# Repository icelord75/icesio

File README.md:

# iCESIO

**A replacement brain for the CASIO 3208 module** — the one inside the CA-53W and CA-506 calculator watches.
iCESIO keeps the original case, LCD, keypad and buzzer, and swaps the stock chip for a PIC16 microcontroller
with an accelerometer, a compass, an environmental sensor and a full RGB backlight.

<p align="center">
  
  &nbsp;&nbsp;
  
</p>

> **Status:** work in progress. The hardware (rev. V2) is done; the firmware shows and sets the time,
> beeps and talks to the sensors over I²C. Most of the watch features listed below are still to come.

---

## Contents

- [Hardware](#hardware)
- [Firmware](#firmware)
  - [What works](#what-works)
  - [Using the watch](#using-the-watch)
  - [Building](#building)
  - [Configuration](#configuration)
- [Repository layout](#repository-layout)
- [Known issues](#known-issues)
- [Roadmap](#roadmap)
- [Related projects](#related-projects)
- [License](#license)

---

## Hardware

| Function       | Part                                                              | Notes                                         |
|----------------|-------------------------------------------------------------------|-----------------------------------------------|
| MCU            | Microchip **PIC16F19197**                                         | 8-bit, 56 KB flash, 4 KB RAM, 256 B EEPROM, LCD driver, RTCC |
| EEPROM         | Microchip **24CW1280T-I/CS0668**                                  | 16 KB, WLCSP                                  |
| Accelerometer  | NXP **MMA8451QT**                                                 | 3-axis, 14-bit / 8-bit                        |
| Compass        | Honeywell **HMC5883L** or Isentek **IST8310**                     | 3-axis magnetometer                           |
| Environment    | Bosch **BME280**                                                  | temperature, humidity, pressure               |
| RGB backlight  | ON Semi **NCP5623CMUTBG** + Songxin **SX-0402-RGB**               | I²C triple LED driver, 0404 RGB LED           |
| Battery        | **CR2016**                                                        | CR2020 / CR2025 / CR2320 might fit            |

All peripherals share one I²C bus. A 19200 bps TTL UART is available for debugging.

<p align="center">
  
</p>

### Connections to the CASIO module

| CASIO pad      | MCU pin          | Use                                                      |
|----------------|------------------|----------------------------------------------------------|
| MODE           | RH0              | side button, active low (connects to GND, weak pull-up)  |
| PRGM           | RH1              | side button, active low (connects to GND, weak pull-up)  |
| SIG            | RG0 (PWM3 via PPS) | buzzer, through T1 (PDTC114) and the coil L1           |
| K2…K5          | RG1, RG2, RG3, RF7 | keypad rows (driven low)                               |
| K6…K9          | RC7, RC6, RC0, RC1 | keypad columns (inputs, weak pull-ups)                 |
| LCD_S0…S30, C0…C3 | LCD SEG/COM pins | 4-COM multiplexed LCD                                |

---

## Firmware

MPLAB X project in [`icesio.X/`](icesio.X), written in C for **MPLAB XC8**. Peripheral setup is generated
by MPLAB Code Configurator (`icesio.mc3`, [`mcc_generated_files/`](icesio.X/mcc_generated_files)).

| Module                                   | What it does                                                        |
|------------------------------------------|---------------------------------------------------------------------|
| [`main.c`](icesio.X/main.c)              | power-on self test over UART, main loop (100 ms tick)               |
| [`clock.c`](icesio.X/clock.c)            | time screen and time / date setting                                 |
| [`buttons.c`](icesio.X/buttons.c)        | MODE / PRGM debouncing, auto-repeat                                 |
| [`beep.c`](icesio.X/beep.c)              | buzzer: ~4 kHz hardware PWM, key click                              |
| [`keypad.c`](icesio.X/keypad.c)          | 4×4 keypad matrix scan with debouncing                              |
| [`lcd.c`](icesio.X/lcd.c)                | 7-segment font and table-driven LCD segment mapping                 |
| [`led.c`](icesio.X/led.c)                | NCP5623C RGB LED driver                                             |
| [`bme280.c`](icesio.X/bme280.c)          | BME280 temperature / humidity / pressure                            |
| [`mma8451.c`](icesio.X/mma8451.c)        | MMA8451 accelerometer (based on [yangosoft/pic_mma8451](https://github.com/yangosoft/pic_mma8451)) |
| [`compass.c`](icesio.X/compass.c)        | HMC5883L compass (disabled for now)                                 |
| [`uart.c`](icesio.X/uart.c), [`debug.h`](icesio.X/debug.h) | debug output: `DBG_PRINT()` / `DBG_PRINTF()`, compiled only with `DEBUG` |

### What works

- [x] Power-on self test with progress on the debug UART (`DEBUG` builds)
- [x] Time display with a blinking colon and the day of month
- [x] Setting time and date with the side buttons or the keypad
- [x] Rate correction in s/day, stored in EEPROM
- [x] Key click on the buzzer
- [x] 4×4 keypad driver (test mode shows the pressed key)
- [x] RGB LED, BME280, MMA8451 and HMC5883L drivers
- [ ] Alarms, stopwatch, timer, calculator… — see the [roadmap](#roadmap)

### Using the watch

```
digit:  0 1 2 3 4 5 6 7     9 10
time:   H H : M M   S S     D  D      D D = day of month
date:   D D - M M - Y Y               shown while setting the date
```

| Mode        | Button   | Action                                                                 |
|-------------|----------|------------------------------------------------------------------------|
| Time        | **PRGM** | enter setting mode                                                     |
| Setting     | **PRGM** | next field: hour → minute → second → year → month → day → rate correction → done |
| Setting     | **MODE** | +1 to the blinking field; hold to scroll                               |
| Seconds     | **MODE** | reset to `00` and start the clock right away — press it on the time signal |
| Setting     | **0…9**  | type the field: two digits set it and jump to the next field (`1_` after the first digit) |
| Setting     | **=**    | same as PRGM; a single typed digit counts as `0x`                      |
| Setting     | **+ / −** | +1 / −1 to the field (on seconds: reset to `00`)                      |
| Setting     | **.**    | finish setting                                                         |
| Correction  | **MODE / +**, **−** | rate correction ±1 s/day; hold to repeat, after 3 s in steps of 10 |

Keypad (from the goodwatch firmware for the same module, matches the CA-53W):

|        | K6 | K7 | K8 | K9 |
|--------|:--:|:--:|:--:|:--:|
| **K5** | 7  | 8  | 9  | ÷  |
| **K4** | 4  | 5  | 6  | ×  |
| **K3** | 1  | 2  | 3  | −  |
| **K2** | 0  | .  | =  | +  |

With `KEYPAD_TEST` on, a key pressed on the time screen is shown as `KEY    7` for one second.

Typed values are checked: hours 00–23, minutes and seconds 00–59, year 00–99, month 01–12, and the day
must exist in that month (no 31 April, 29 February only in leap years). An impossible value is rejected
with a long beep. Typing the seconds starts the clock at the entered time immediately.

### Rate correction

Without a 32.768 kHz crystal the clock runs from the internal MFINTOSC, which can be off by up to ~2 %
(about ±1700 s/day). The last setting field, `Cor  -12`, holds a correction in **seconds per day**
(−1999…+1999), saved in the data EEPROM:

1. Set the time exactly and note how many seconds the watch gains or loses over a day or more.
2. Enter the measured drift per day with the opposite sign: the watch **gains** 12 s/day → `Cor -12`;
   it **loses** 300 s/day → `Cor 300`.

The firmware then moves the RTCC seconds by one every 86400 / |Cor| seconds, so the watch stays within
about a second. (The hardware `RTCCAL` register only reaches about ±6 s/day, too little for MFINTOSC.)

Setting mode also ends after 60 s without a press; changes are kept. Only the fields you changed are
written back, so entering and leaving setting mode never makes the clock lose time. The day of the week
is calculated automatically.

### Building

Requirements:

- [MPLAB X IDE](https://www.microchip.com/mplab/mplab-x-ide) (tested with v6.35)
- [MPLAB XC8](https://www.microchip.com/mplab/compilers) **v3.10**
- Device pack **PIC16F1xxxx_DFP 1.7.146**

Open `icesio.X` in MPLAB X and build, or from the command line (after MPLAB X has generated
`nbproject/Makefile-local-default.mk` for your machine):

```bash
cd icesio.X
make -f nbproject/Makefile-default.mk CONF=default .build-conf
```

Current size: **~6.0 K of 32 K words** program memory (18 %), **324 B** RAM; with `DEBUG` ~11.7 K (printf).

### Configuration

Compile-time switches, all at the top of their source files:

| Define              | File        | Default | Meaning                                                    |
|---------------------|-------------|---------|------------------------------------------------------------|
| `CLOCK_24H`         | `clock.c`   | `1`     | 24-hour display; `0` for 12-hour with AM/PM                 |
| `KEY_BEEP`          | `clock.c`   | `1`     | click on every button / key press                          |
| `KEYPAD_TEST`       | `clock.c`   | `1`     | show the pressed key on the time screen                    |
| `KEYPAD_ROW_K2`     | `keypad.c`  | `1`     | scan the bottom row on RG1; `0` keeps RG1 as UART TX       |
| `SET_TIMEOUT_S`     | `clock.c`   | `60`    | leave setting mode after this many seconds                 |
| `BTN_ACTIVE_LOW`    | `buttons.c` | `1`     | buttons connect to GND (`1`, as on goodwatch) or to + (`0`) |
| `BTN_SOFT_PULLDOWN` | `buttons.c` | `1`     | with `BTN_ACTIVE_LOW 0` only: software pull-down (no resistors to GND) |
| `BEEP_PR`           | `beep.c`    | `14`    | tone: 62.5 kHz / (`BEEP_PR` + 1) ≈ 4167 Hz                 |
| `BEEP_CLICK_MS`     | `beep.c`    | `30`    | key click length                                           |
| `USE_COMPASS`       | `main.c`    | `0`     | initialise and poll the compass                            |
| `DEBUG`             | `debug.h`   | off     | self-test log and a sensor dump every second on the UART (19200 bps, RG1) |
| `COR_MAX`           | `clock.c`   | `1999`  | rate correction limit, s/day                               |

---

## Repository layout

```
icesio.X/              firmware (MPLAB X project)
hardware/
  icesio.sch/.brd      Eagle, rev. V1
  icesio_V2.sch/.brd   Eagle, rev. V2
  icesio_V2/           rev. V2 imported into KiCad
  CHAGE LIST           V1 → V2 changes
kicad/                 KiCad import of icesio0
icesio0.*, icesio2.*   Eagle snapshots (2019)
icesio2_2019-03-12.zip Gerber + drill files of the 2019-03-12 board
icesio.docx            draft of the operation guide
front.png, back.png    board renders
schematic.png          schematic, rev. V2
```

---

## Known issues

- **RTCC runs from MFINTOSC.** The SOSC crystal pins are used by the keypad, so the clock runs from the
  internal oscillator (about ±1–2 %, and it drifts with temperature). The [rate correction](#rate-correction)
  compensates the average error; a 32.768 kHz crystal is planned for the next board revision.
- **SEG17 / SEG20 share the ICSP CLK / DAT pins.** Eight segments are lost while debugging
  (`#ifndef __DEBUG` in `lcd.c`). To be rerouted in the next revision.
- **Debug UART vs. keypad.** K2 (RG1) is also the EUSART2 TX pin. The UART exists only in `DEBUG` builds;
  normal builds switch EUSART2 off and give RG1 to the keypad, debug builds keep the UART there and don't
  scan the bottom row (0 . = +).
- **SOSC and LCD pins used by the keypad.** `Keypad_Init()` switches off the secondary oscillator
  (RC0/RC1) and the unused LCD segments SEG27/SEG28 (RC6/RC7) that MCC had enabled.
- The keypad layout comes from goodwatch and has not been checked on this board yet.

---

## Roadmap

- **Controls:** 2 side buttons + 4×4 keypad
- **Timekeeping:** home and world time with automatic DST and assisted calibration
- **Perpetual calendar** up to 2199
- **Calculator:** infix, prefix or RPN (configurable), ±9.9999999 × 10<sup>99</sup> (8-digit mantissa)
- **Alarm:** 5 daily + 5 weekly alarms, hourly signal
- **Stopwatch:** 5 stopwatches up to 23:59:59.99, 0.01 s resolution
- **Timer:** 5 countdown timers up to 99:59:59
- **Signals:** RTTTL melodies for alarms and timers; minute repeater
- **Backlight:** full RGB, separate colours for alarms and timers
- **Sun and Moon:** sunrise / sunset (latitude presets + time zone), precise Moon phase, equation of time
- **Accelerometer:** tap control, tilt sensor, speedometer, 0–100 km/h timing
- **Compass:** regular compass, angle finder
- **Environment:** temperature (°C / °F), humidity, barometer (hPa, mbar, at, atm, Torr, mmHg, PSI, inHg),
  with hour / 12 h / 24 h trends

---

## Related projects

- [**goodwatch**](https://github.com/travisgoodspeed/goodwatch) — replacement board for the same CASIO 3208
  module (CA-53W, CA-506), based on the CC430
- [**Pluto**](https://github.com/carrotIndustries/pluto) — replacement PCB for the CASIO F-91W, based on an MSP430

---

## License

[MIT](LICENSE) © icelord75 — firmware, hardware design files and documentation.

Exceptions: files in [`icesio.X/mcc_generated_files/`](icesio.X/mcc_generated_files) are generated by
MPLAB Code Configurator and covered by Microchip's license terms in their headers;
[`mma8451.c`](icesio.X/mma8451.c) is based on [yangosoft/pic_mma8451](https://github.com/yangosoft/pic_mma8451).

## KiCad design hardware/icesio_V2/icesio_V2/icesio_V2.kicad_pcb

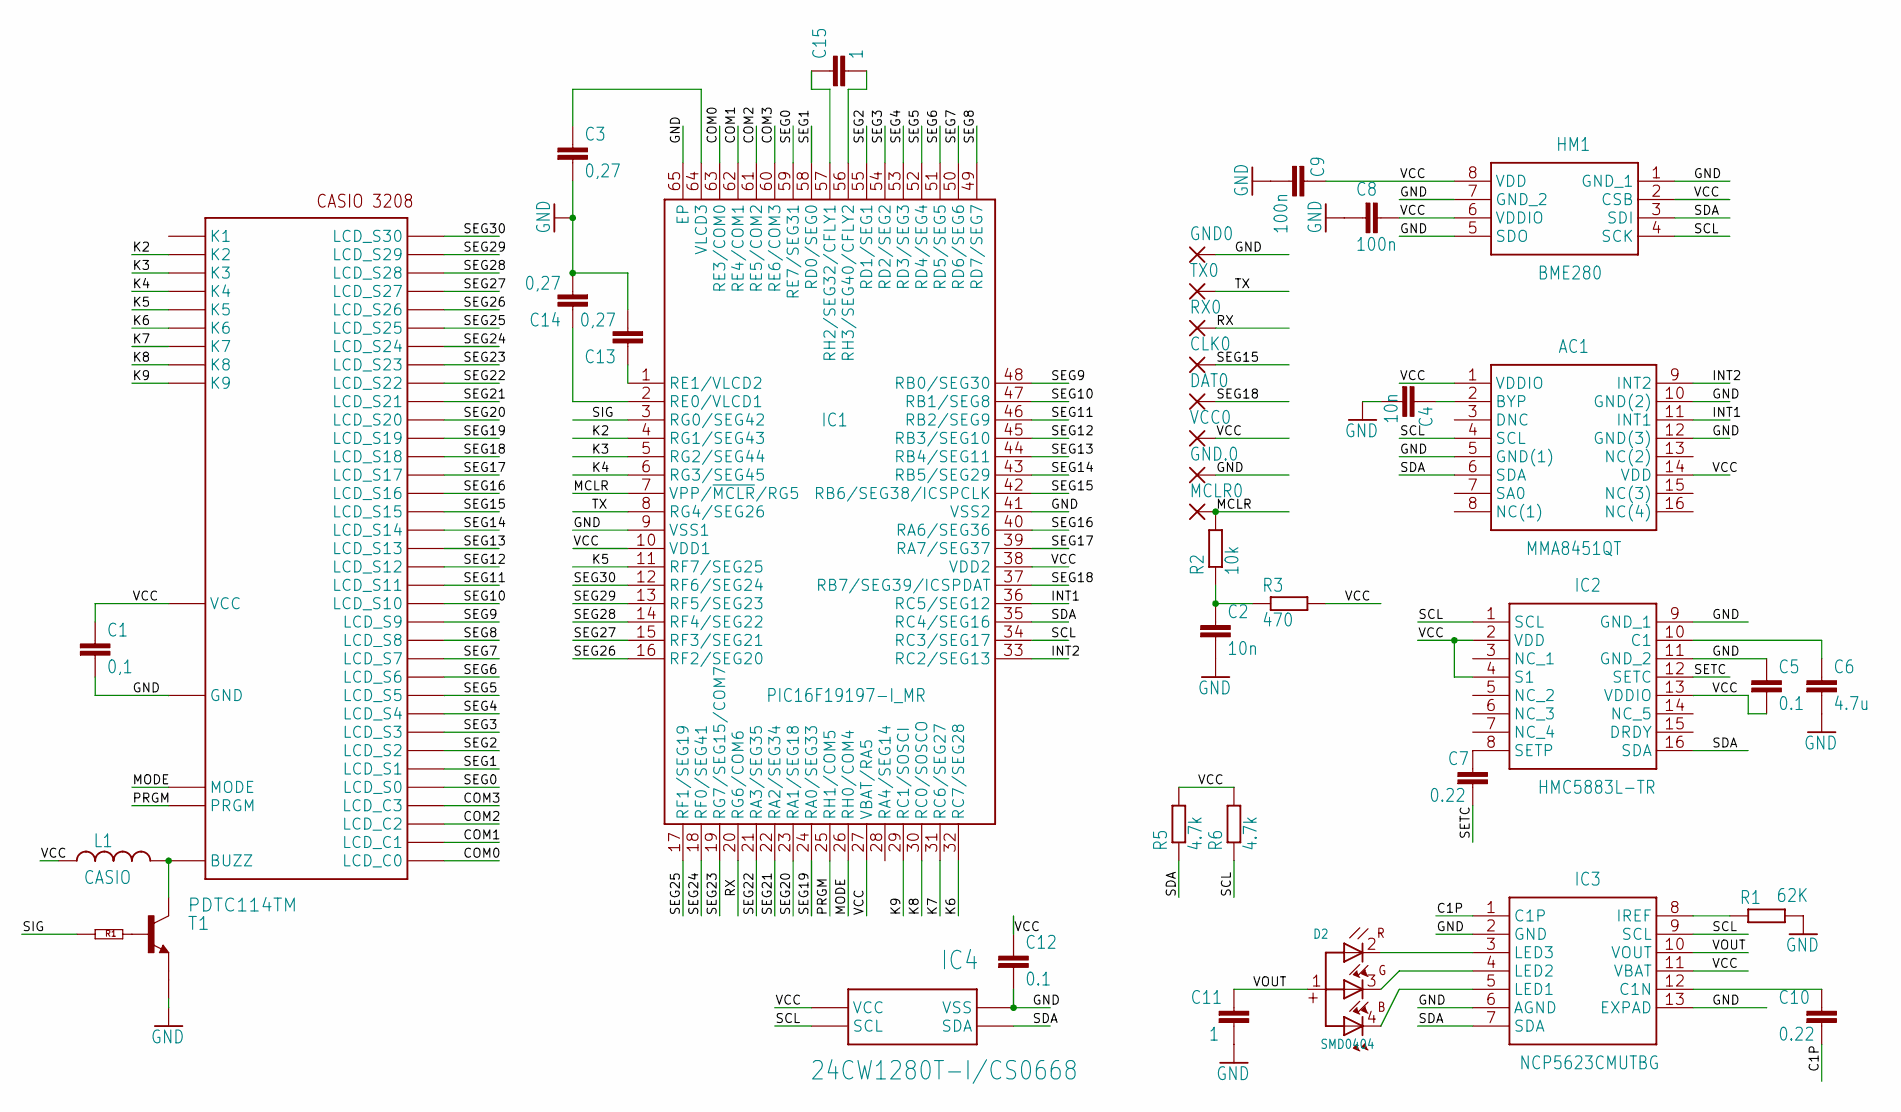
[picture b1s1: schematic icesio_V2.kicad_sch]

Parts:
AC1: MMA8451QT; PQFN50P300X300X100-16N
C1: 0,1; RESC0402_L
C2, C4: 10n; RESC0402_L
C3, C13, C14: 0,27; RESC0402_L
C5, C12: 0.1; RESC0402_L
C6: 4.7u; RESC0402_L
C7, C10: 0.22; RESC0402_L
C8, C9: 100n; RESC0402_L
C11, C15: 1; RESC0402_L
CLK0: WIREPADSMD1,27-254; SMD1,27-2,54
D2: SMD0404; WL-SFCC_0404
DAT0: WIREPADSMD1,27-254; SMD1,27-2,54
GND0, GND.0: WIREPADSMD1,27-254; SMD1,27-2,54
HM1: BME280
IC1: PIC16F19197-I_MR; QFN50P900X900X100-65N
IC2: HMC5883L-TR; 16-PIN-LPCC
IC3: NCP5623CMUTBG; NCP5623BMUTBG
IC4: 24CW1280T-I/CS0668; CSP
L1: CASIO; L4516C
MCLR0: WIREPADSMD1,27-254; SMD1,27-2,54
R1: 62K; R0402
R2: 10k; R0402
R3: 470; R0402
R5, R6: 4.7k; R0402
RX0: WIREPADSMD1,27-254; SMD1,27-2,54
T1: PDTC114TM; SOT883(B)
TX0: WIREPADSMD1,27-254; SMD1,27-2,54
U$1: CASIO3208
VCC0: WIREPADSMD1,27-254; SMD1,27-2,54

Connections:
BUZ: L1.2, T1.3 (C), U$1.BUZZ
BYP: AC1.2 (BYP), C4.1
C1: C6.1, IC2.10 (C1)
C1P: C10.2, IC3.1 (C1P)
CFLY1: C15.1, IC1.57 (RH2/SEG32/CFLY1)
CFLY2: C15.2, IC1.56 (RH3/SEG40/CFLY2)
COM0: IC1.63 (RE3/COM0), U$1.LCD1 (LCD_C0)
COM1: IC1.62 (RE4/COM1), U$1.LCD2 (LCD_C1)
COM2: IC1.61 (RE5/COM2), U$1.LCD3 (LCD_C2)
COM3: IC1.60 (RE6/COM3), U$1.LCD4 (LCD_C3)
GND: AC1.5 (GND(1)), AC1.10 (GND(2)), AC1.12 (GND(3)), C1.2, C2.2, C3.2, C4.2, C5.1, C6.2, C8.2, C9.2, C11.2, C12.2, C13.2, C14.2, GND0.1, GND.0.1, HM1.1 (GND_1), HM1.5 (SDO), HM1.7 (GND_2), IC1.9 (VSS1), IC1.41 (VSS2), IC1.65 (EP), IC2.9 (GND_1), IC2.11 (GND_2), IC3.2 (GND), IC3.6 (AGND), IC3.13 (EXPAD), IC4.VSS, R1.2, T1.2 (E), U$1.GND
INT1: AC1.11 (INT1), IC1.36 (RC5/SEG12)
INT2: AC1.9 (INT2), IC1.33 (RC2/SEG13)
K2: IC1.4 (RG1/SEG43), U$1.K2
K3: IC1.5 (RG2/SEG44), U$1.K3
K4: IC1.6 (RG3/SEG45), U$1.K4
K5: IC1.11 (RF7/SEG25), U$1.K5
K6: IC1.32 (RC7/SEG28), U$1.K6
K7: IC1.31 (RC6/SEG27), U$1.K7
K8: IC1.30 (RC0/SOSCO), U$1.K8
K9: IC1.29 (RC1/SOSCI), U$1.K9
MCLR: IC1.7 (VPP/~MCLR/RG5), MCLR0.1, R2.2
MCLRVCC: C2.1, R2.1, R3.1
MODE: IC1.26 (RH0/COM4), U$1.MODE
unnamed: D2.2 (R), IC3.3 (LED3)
unnamed: C7.1, IC2.8 (SETP)
unnamed: D2.3 (G), IC3.4 (LED2)
unnamed: D2.4 (B), IC3.5 (LED1)
unnamed: IC3.8 (IREF), R1.1
unnamed: C10.1, IC3.12 (C1N)
PRGM: IC1.25 (RH1/COM5), U$1.PRGM
RX: IC1.20 (RG6/COM6), RX0.1
SCL: AC1.4 (SCL), HM1.4 (SCK), IC1.34 (RC3/SEG17), IC2.1 (SCL), IC3.9 (SCL), IC4.SCL, R6.1
SDA: AC1.6 (SDA), HM1.3 (SDI), IC1.35 (RC4/SEG16), IC2.16 (SDA), IC3.7 (SDA), IC4.SDA, R5.1
SEG0: IC1.59 (RE7/SEG31), U$1.LCD5 (LCD_S0)
SEG1: IC1.58 (RD0/SEG0), U$1.LCD6 (LCD_S1)
SEG2: IC1.55 (RD1/SEG1), U$1.LCD7 (LCD_S2)
SEG3: IC1.54 (RD2/SEG2), U$1.LCD8 (LCD_S3)
SEG4: IC1.53 (RD3/SEG3), U$1.LCD9 (LCD_S4)
SEG5: IC1.52 (RD4/SEG4), U$1.LCD10 (LCD_S5)
SEG6: IC1.51 (RD5/SEG5), U$1.LCD11 (LCD_S6)
SEG7: IC1.50 (RD6/SEG6), U$1.LCD12 (LCD_S7)
SEG8: IC1.49 (RD7/SEG7), U$1.LCD13 (LCD_S8)
SEG9: IC1.48 (RB0/SEG30), U$1.LCD14 (LCD_S9)
SEG10: IC1.47 (RB1/SEG8), U$1.LCD15 (LCD_S10)
SEG11: IC1.46 (RB2/SEG9), U$1.LCD16 (LCD_S11)
SEG12: IC1.45 (RB3/SEG10), U$1.LCD17 (LCD_S12)
SEG13: IC1.44 (RB4/SEG11), U$1.LCD18 (LCD_S13)
SEG14: IC1.43 (RB5/SEG29), U$1.LCD19 (LCD_S14)
SEG15: CLK0.1, IC1.42 (RB6/SEG38/ICSPCLK), U$1.LCD20 (LCD_S15)
SEG16: IC1.40 (RA6/SEG36), U$1.LCD21 (LCD_S16)
SEG17: IC1.39 (RA7/SEG37), U$1.LCD22 (LCD_S17)
SEG18: DAT0.1, IC1.37 (RB7/SEG39/ICSPDAT), U$1.LCD23 (LCD_S18)
SEG19: IC1.24 (RA0/SEG33), U$1.LCD24 (LCD_S19)
SEG20: IC1.23 (RA1/SEG18), U$1.LCD25 (LCD_S20)
SEG21: IC1.22 (RA2/SEG34), U$1.LCD26 (LCD_S21)
SEG22: IC1.21 (RA3/SEG35), U$1.LCD27 (LCD_S22)
SEG23: IC1.19 (RG7/SEG15/COM7), U$1.LCD28 (LCD_S23)
SEG24: IC1.18 (RF0/SEG41), U$1.LCD29 (LCD_S24)
SEG25: IC1.17 (RF1/SEG19), U$1.LCD30 (LCD_S25)
SEG26: IC1.16 (RF2/SEG20), U$1.LCD31 (LCD_S26)
SEG27: IC1.15 (RF3/SEG21), U$1.LCD32 (LCD_S27)
SEG28: IC1.14 (RF4/SEG22), U$1.LCD33 (LCD_S28)
SEG29: IC1.13 (RF5/SEG23), U$1.LCD34 (LCD_S29)
SEG30: IC1.12 (RF6/SEG24), U$1.LCD35 (LCD_S30)
SETC: C7.2, IC2.12 (SETC)
SIG: IC1.3 (RG0/SEG42), T1.1 (INPUT)
TX: IC1.8 (RG4/SEG26), TX0.1
VCC: AC1.1 (VDDIO), AC1.14 (VDD), C1.1, C5.2, C8.1, C9.1, C12.1, HM1.2 (CSB), HM1.6 (VDDIO), HM1.8 (VDD), IC1.10 (VDD1), IC1.27 (VBAT/RA5), IC1.38 (VDD2), IC2.2 (VDD), IC2.4 (S1), IC2.13 (VDDIO), IC3.11 (VBAT), IC4.VCC, L1.1, R3.2, R5.2, R6.2, U$1.VCC, VCC0.1
VLCD1: C14.1, IC1.2 (RE0/VLCD1)
VLCD2: C13.1, IC1.1 (RE1/VLCD2)
VLCD3: C3.1, IC1.64 (VLCD3)
VOUT: C11.1, D2.1, IC3.10 (VOUT)

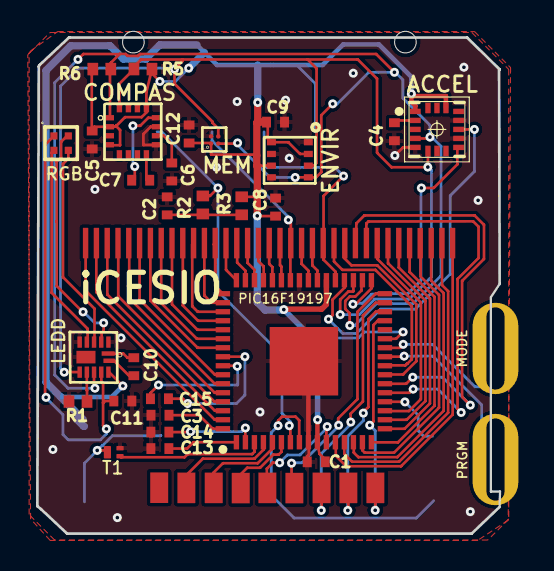
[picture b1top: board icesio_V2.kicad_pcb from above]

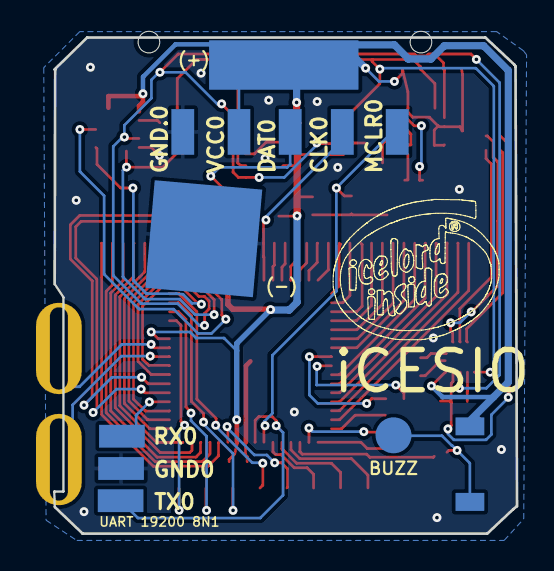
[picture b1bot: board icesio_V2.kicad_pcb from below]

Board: 2 copper layers, 25.7 x 27.6 mm, 39 parts (10 on the bottom side), 73 nets.

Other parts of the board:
U$2: ICELORD_SMALL

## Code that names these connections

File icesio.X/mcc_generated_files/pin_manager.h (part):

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#define RA0_SetHigh()            do { LATAbits.LATA0 = 1; } while(0)
#define RA0_SetLow()             do { LATAbits.LATA0 = 0; } while(0)
#define RA0_Toggle()             do { LATAbits.LATA0 = ~LATAbits.LATA0; } while(0)
#define RA0_GetValue()              PORTAbits.RA0
#define RA0_SetDigitalInput()    do { TRISAbits.TRISA0 = 1; } while(0)
#define RA0_SetDigitalOutput()   do { TRISAbits.TRISA0 = 0; } while(0)
#define RA0_SetPullup()             do { WPUAbits.WPUA0 = 1; } while(0)
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#define RA1_SetHigh()            do { LATAbits.LATA1 = 1; } while(0)
#define RA1_SetLow()             do { LATAbits.LATA1 = 0; } while(0)
#define RA1_Toggle()             do { LATAbits.LATA1 = ~LATAbits.LATA1; } while(0)
#define RA1_GetValue()              PORTAbits.RA1
#define RA1_SetDigitalInput()    do { TRISAbits.TRISA1 = 1; } while(0)
#define RA1_SetDigitalOutput()   do { TRISAbits.TRISA1 = 0; } while(0)
#define RA1_SetPullup()             do { WPUAbits.WPUA1 = 1; } while(0)
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#define RA2_SetHigh()            do { LATAbits.LATA2 = 1; } while(0)
#define RA2_SetLow()             do { LATAbits.LATA2 = 0; } while(0)
#define RA2_Toggle()             do { LATAbits.LATA2 = ~LATAbits.LATA2; } while(0)
#define RA2_GetValue()              PORTAbits.RA2
#define RA2_SetDigitalInput()    do { TRISAbits.TRISA2 = 1; } while(0)
#define RA2_SetDigitalOutput()   do { TRISAbits.TRISA2 = 0; } while(0)
#define RA2_SetPullup()             do { WPUAbits.WPUA2 = 1; } while(0)
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#define RA3_SetHigh()            do { LATAbits.LATA3 = 1; } while(0)
#define RA3_SetLow()             do { LATAbits.LATA3 = 0; } while(0)
#define RA3_Toggle()             do { LATAbits.LATA3 = ~LATAbits.LATA3; } while(0)
#define RA3_GetValue()              PORTAbits.RA3
#define RA3_SetDigitalInput()    do { TRISAbits.TRISA3 = 1; } while(0)
#define RA3_SetDigitalOutput()   do { TRISAbits.TRISA3 = 0; } while(0)
#define RA3_SetPullup()             do { WPUAbits.WPUA3 = 1; } while(0)
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#define RA6_SetHigh()            do { LATAbits.LATA6 = 1; } while(0)
#define RA6_SetLow()             do { LATAbits.LATA6 = 0; } while(0)
#define RA6_Toggle()             do { LATAbits.LATA6 = ~LATAbits.LATA6; } while(0)
#define RA6_GetValue()              PORTAbits.RA6
#define RA6_SetDigitalInput()    do { TRISAbits.TRISA6 = 1; } while(0)
#define RA6_SetDigitalOutput()   do { TRISAbits.TRISA6 = 0; } while(0)
#define RA6_SetPullup()             do { WPUAbits.WPUA6 = 1; } while(0)
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#define RA7_SetHigh()            do { LATAbits.LATA7 = 1; } while(0)
#define RA7_SetLow()             do { LATAbits.LATA7 = 0; } while(0)
#define RA7_Toggle()             do { LATAbits.LATA7 = ~LATAbits.LATA7; } while(0)
#define RA7_GetValue()              PORTAbits.RA7
#define RA7_SetDigitalInput()    do { TRISAbits.TRISA7 = 1; } while(0)
#define RA7_SetDigitalOutput()   do { TRISAbits.TRISA7 = 0; } while(0)
#define RA7_SetPullup()             do { WPUAbits.WPUA7 = 1; } while(0)
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#define RB0_SetHigh()            do { LATBbits.LATB0 = 1; } while(0)
#define RB0_SetLow()             do { LATBbits.LATB0 = 0; } while(0)
#define RB0_Toggle()             do { LATBbits.LATB0 = ~LATBbits.LATB0; } while(0)
#define RB0_GetValue()              PORTBbits.RB0
#define RB0_SetDigitalInput()    do { TRISBbits.TRISB0 = 1; } while(0)
#define RB0_SetDigitalOutput()   do { TRISBbits.TRISB0 = 0; } while(0)
#define RB0_SetPullup()             do { WPUBbits.WPUB0 = 1; } while(0)
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#define RB1_SetHigh()            do { LATBbits.LATB1 = 1; } while(0)
#define RB1_SetLow()             do { LATBbits.LATB1 = 0; } while(0)
#define RB1_Toggle()             do { LATBbits.LATB1 = ~LATBbits.LATB1; } while(0)
#define RB1_GetValue()              PORTBbits.RB1
#define RB1_SetDigitalInput()    do { TRISBbits.TRISB1 = 1; } while(0)
#define RB1_SetDigitalOutput()   do { TRISBbits.TRISB1 = 0; } while(0)
#define RB1_SetPullup()             do { WPUBbits.WPUB1 = 1; } while(0)
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#define RB2_SetHigh()            do { LATBbits.LATB2 = 1; } while(0)
#define RB2_SetLow()             do { LATBbits.LATB2 = 0; } while(0)
#define RB2_Toggle()             do { LATBbits.LATB2 = ~LATBbits.LATB2; } while(0)
#define RB2_GetValue()              PORTBbits.RB2
#define RB2_SetDigitalInput()    do { TRISBbits.TRISB2 = 1; } while(0)
#define RB2_SetDigitalOutput()   do { TRISBbits.TRISB2 = 0; } while(0)
#define RB2_SetPullup()             do { WPUBbits.WPUB2 = 1; } while(0)
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#define RB3_SetHigh()            do { LATBbits.LATB3 = 1; } while(0)
#define RB3_SetLow()             do { LATBbits.LATB3 = 0; } while(0)
#define RB3_Toggle()             do { LATBbits.LATB3 = ~LATBbits.LATB3; } while(0)
#define RB3_GetValue()              PORTBbits.RB3
#define RB3_SetDigitalInput()    do { TRISBbits.TRISB3 = 1; } while(0)
#define RB3_SetDigitalOutput()   do { TRISBbits.TRISB3 = 0; } while(0)
#define RB3_SetPullup()             do { WPUBbits.WPUB3 = 1; } while(0)
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#define RB4_SetHigh()            do { LATBbits.LATB4 = 1; } while(0)
#define RB4_SetLow()             do { LATBbits.LATB4 = 0; } while(0)
#define RB4_Toggle()             do { LATBbits.LATB4 = ~LATBbits.LATB4; } while(0)
#define RB4_GetValue()              PORTBbits.RB4
#define RB4_SetDigitalInput()    do { TRISBbits.TRISB4 = 1; } while(0)
#define RB4_SetDigitalOutput()   do { TRISBbits.TRISB4 = 0; } while(0)
#define RB4_SetPullup()             do { WPUBbits.WPUB4 = 1; } while(0)
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#define RB5_SetHigh()            do { LATBbits.LATB5 = 1; } while(0)
#define RB5_SetLow()             do { LATBbits.LATB5 = 0; } while(0)
#define RB5_Toggle()             do { LATBbits.LATB5 = ~LATBbits.LATB5; } while(0)
#define RB5_GetValue()              PORTBbits.RB5
#define RB5_SetDigitalInput()    do { TRISBbits.TRISB5 = 1; } while(0)
#define RB5_SetDigitalOutput()   do { TRISBbits.TRISB5 = 0; } while(0)
#define RB5_SetPullup()             do { WPUBbits.WPUB5 = 1; } while(0)
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#define RB6_SetHigh()            do { LATBbits.LATB6 = 1; } while(0)
#define RB6_SetLow()             do { LATBbits.LATB6 = 0; } while(0)
#define RB6_Toggle()             do { LATBbits.LATB6 = ~LATBbits.LATB6; } while(0)
#define RB6_GetValue()              PORTBbits.RB6
#define RB6_SetDigitalInput()    do { TRISBbits.TRISB6 = 1; } while(0)
#define RB6_SetDigitalOutput()   do { TRISBbits.TRISB6 = 0; } while(0)
#define RB6_SetPullup()             do { WPUBbits.WPUB6 = 1; } while(0)
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#define RB7_SetHigh()            do { LATBbits.LATB7 = 1; } while(0)
#define RB7_SetLow()             do { LATBbits.LATB7 = 0; } while(0)
#define RB7_Toggle()             do { LATBbits.LATB7 = ~LATBbits.LATB7; } while(0)
#define RB7_GetValue()              PORTBbits.RB7
#define RB7_SetDigitalInput()    do { TRISBbits.TRISB7 = 1; } while(0)
#define RB7_SetDigitalOutput()   do { TRISBbits.TRISB7 = 0; } while(0)
#define RB7_SetPullup()             do { WPUBbits.WPUB7 = 1; } while(0)
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// get/set IO_RC0 aliases
#define IO_RC0_TRIS                 TRISCbits.TRISC0
#define IO_RC0_LAT                  LATCbits.LATC0
#define IO_RC0_PORT                 PORTCbits.RC0
#define IO_RC0_WPU                  WPUCbits.WPUC0
#define IO_RC0_OD                   ODCONCbits.ODCC0
#define IO_RC0_ANS                  ANSELCbits.ANSC0
#define IO_RC0_SetHigh()            do { LATCbits.LATC0 = 1; } while(0)
#define IO_RC0_SetLow()             do { LATCbits.LATC0 = 0; } while(0)
#define IO_RC0_Toggle()             do { LATCbits.LATC0 = ~LATCbits.LATC0; } while(0)
#define IO_RC0_GetValue()           PORTCbits.RC0
#define IO_RC0_SetDigitalInput()    do { TRISCbits.TRISC0 = 1; } while(0)
#define IO_RC0_SetDigitalOutput()   do { TRISCbits.TRISC0 = 0; } while(0)
#define IO_RC0_SetPullup()          do { WPUCbits.WPUC0 = 1; } while(0)
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// get/set IO_RC1 aliases
#define IO_RC1_TRIS                 TRISCbits.TRISC1
#define IO_RC1_LAT                  LATCbits.LATC1
#define IO_RC1_PORT                 PORTCbits.RC1
#define IO_RC1_WPU                  WPUCbits.WPUC1
#define IO_RC1_OD                   ODCONCbits.ODCC1
#define IO_RC1_ANS                  ANSELCbits.ANSC1
#define IO_RC1_SetHigh()            do { LATCbits.LATC1 = 1; } while(0)
#define IO_RC1_SetLow()             do { LATCbits.LATC1 = 0; } while(0)
#define IO_RC1_Toggle()             do { LATCbits.LATC1 = ~LATCbits.LATC1; } while(0)
#define IO_RC1_GetValue()           PORTCbits.RC1
#define IO_RC1_SetDigitalInput()    do { TRISCbits.TRISC1 = 1; } while(0)
#define IO_RC1_SetDigitalOutput()   do { TRISCbits.TRISC1 = 0; } while(0)
#define IO_RC1_SetPullup()          do { WPUCbits.WPUC1 = 1; } while(0)
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#define RC3_SetHigh()            do { LATCbits.LATC3 = 1; } while(0)
#define RC3_SetLow()             do { LATCbits.LATC3 = 0; } while(0)
#define RC3_Toggle()             do { LATCbits.LATC3 = ~LATCbits.LATC3; } while(0)
#define RC3_GetValue()              PORTCbits.RC3
#define RC3_SetDigitalInput()    do { TRISCbits.TRISC3 = 1; } while(0)
#define RC3_SetDigitalOutput()   do { TRISCbits.TRISC3 = 0; } while(0)
#define RC3_SetPullup()             do { WPUCbits.WPUC3 = 1; } while(0)
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#define RC4_SetHigh()            do { LATCbits.LATC4 = 1; } while(0)
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
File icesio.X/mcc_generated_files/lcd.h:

/**
  LCD Generated Driver API Header File
  
  @Company
    Microchip Technology Inc.

  @File Name
    lcd.h
	
  @Summary
    This is the generated header file for the LCD driver using PIC10 / PIC12 / PIC16 / PIC18 MCUs

  @Description
    This header file provides APIs for driver for LCD.
    Generation Information :
        Product Revision  :  PIC10 / PIC12 / PIC16 / PIC18 MCUs - 1.65.2
        Device            :  PIC16F19197
        Driver Version    :  2.01
    The generated drivers are tested against the following:
        Compiler          :  XC8 1.45
        MPLAB 	          :  MPLAB X 4.15
*/

/*
    (c) 2018 Microchip Technology Inc. and its subsidiaries. 
    
    Subject to your compliance with these terms, you may use Microchip software and any 
    derivatives exclusively with Microchip products. It is your responsibility to comply with third party 
    license terms applicable to your use of third party software (including open source software) that 
    may accompany Microchip software.
    
    THIS SOFTWARE IS SUPPLIED BY MICROCHIP "AS IS". NO WARRANTIES, WHETHER 
    EXPRESS, IMPLIED OR STATUTORY, APPLY TO THIS SOFTWARE, INCLUDING ANY 
    IMPLIED WARRANTIES OF NON-INFRINGEMENT, MERCHANTABILITY, AND FITNESS 
    FOR A PARTICULAR PURPOSE.
    
    IN NO EVENT WILL MICROCHIP BE LIABLE FOR ANY INDIRECT, SPECIAL, PUNITIVE, 
    INCIDENTAL OR CONSEQUENTIAL LOSS, DAMAGE, COST OR EXPENSE OF ANY KIND 
    WHATSOEVER RELATED TO THE SOFTWARE, HOWEVER CAUSED, EVEN IF MICROCHIP 
    HAS BEEN ADVISED OF THE POSSIBILITY OR THE DAMAGES ARE FORESEEABLE. TO 
    THE FULLEST EXTENT ALLOWED BY LAW, MICROCHIP'S TOTAL LIABILITY ON ALL 
    CLAIMS IN ANY WAY RELATED TO THIS SOFTWARE WILL NOT EXCEED THE AMOUNT 
    OF FEES, IF ANY, THAT YOU HAVE PAID DIRECTLY TO MICROCHIP FOR THIS 
    SOFTWARE.
*/

#ifndef LCD_H
#define LCD_H

/**
  Section: Included Files
*/

#include <xc.h>
#include <stdbool.h>
    
/**
    Section: Defines
*/ 
   
/**
    Defines: the segments pins
*/
#define SEG00      LCDSE0bits.SE00
#define SEG01      LCDSE0bits.SE01
#define SEG02      LCDSE0bits.SE02
#define SEG03      LCDSE0bits.SE03
#define SEG04      LCDSE0bits.SE04
#define SEG05      LCDSE0bits.SE05
#define SEG06      LCDSE0bits.SE06
#define SEG07      LCDSE0bits.SE07
#define SEG08      LCDSE1bits.SE08
#define SEG09      LCDSE1bits.SE09
#define SEG10      LCDSE1bits.SE10
#define SEG11      LCDSE1bits.SE11
#define SEG12      LCDSE1bits.SE12
#define SEG13      LCDSE1bits.SE13
#define SEG14      LCDSE1bits.SE14
#define SEG15      LCDSE1bits.SE15
#define SEG16      LCDSE2bits.SE16
#define SEG17      LCDSE2bits.SE17
#define SEG18      LCDSE2bits.SE18
#define SEG19      LCDSE2bits.SE19
#define SEG20      LCDSE2bits.SE20
#define SEG21      LCDSE2bits.SE21
#define SEG22      LCDSE2bits.SE22
#define SEG23      LCDSE2bits.SE23
#define SEG24      LCDSE3bits.SE24
#define SEG25      LCDSE3bits.SE25
#define SEG26      LCDSE3bits.SE26
#define SEG27      LCDSE3bits.SE27
#define SEG28      LCDSE3bits.SE28
#define SEG29      LCDSE3bits.SE29
#define SEG30      LCDSE3bits.SE30
#define SEG31      LCDSE3bits.SE31
#define SEG32      LCDSE4bits.SE32
#define SEG33      LCDSE4bits.SE33
#define SEG34      LCDSE4bits.SE34
#define SEG35      LCDSE4bits.SE35
#define SEG36      LCDSE4bits.SE36
#define SEG37      LCDSE4bits.SE37
#define SEG38      LCDSE4bits.SE38
#define SEG39      LCDSE4bits.SE39
#define SEG40      LCDSE5bits.SE40
#define SEG41      LCDSE5bits.SE41
#define SEG42      LCDSE5bits.SE42
#define SEG43      LCDSE5bits.SE43
#define SEG44      LCDSE5bits.SE44
#define SEG45      LCDSE5bits.SE45

#define MACRO_SYM16      LCDDATA12bits.S07C2


/**
    Defines: To Turn on a pixel (a segment from a digit or a special character)
*/
#define MACRO_SYM16ON     MACRO_SYM16 = 1

/**
    Defines: To Turn off a pixel (a segment from a digit or a special character)
*/
#define MACRO_SYM16OFF    MACRO_SYM16 = 0
/**
  Section: Interface Routines
*/

/**
  @Summary
    Initializes the LCD module

  @Description
    This routine should only be called once during system initialization.    

  @Preconditions
    None.

  @Param
    None.

  @Returns
    None.

  @Example
    <code>
    LCD_Initialize();
    </code>     
*/
void LCD_Initialize(void);

/**
    @Summary
        Enable LCD module
        
    @Description
        This routine enables LCD module.   
        
    @Preconditions
        None.

    @Param
        None.

    @Returns
        None.
      
    @Example
        <code>
        LCD_Enable();
        </code>     
*/
void LCD_Enable (void);

/**
    @Summary
        Disable LCD module
        
    @Description
        This routine disables LCD module.   
        
    @Preconditions
        None.

    @Param
        None.

    @Returns
        None.
      
    @Example
        <code>
        LCD_Disable();
        </code>     
*/
void LCD_Disable (void);

/**
    @Summary
        Enable sleep mode for LCD module
        
    @Description
        This routine enables the sleep mode for LCD module.
        
    @Preconditions
        None.

    @Param
        None.

    @Returns
        None.
      
    @Example
        <code>
        LCD_EnableSleepMode();
        </code>     
*/
void LCD_EnableSleepMode (void);

/**
    @Summary
        Disable sleep mode for LCD module
        
    @Description
        This routine disables the sleep mode for LCD module.
        
    @Preconditions
        None.

    @Param
        None.

    @Returns
        None.
      
    @Example
        <code>
        LCD_DisableSleepMode();
        </code>     
*/
void LCD_DisableSleepMode (void);

/**
    @Summary
        Set contrast for LCD module
        
    @Description
        This routine set the contrast value for LCD module.
        
    @Preconditions
       If The internal reference source bit is 0, then the internal LCDcontrast control is unconnected.

    @Param
        Pass the contrast bits value.
        This range for this value is specific for each device.

    @Returns
        None.
      
    @Example
        <code>
        LCD_SetContrast (value);
        </code>     
*/
void LCD_SetContrast (unsigned int value);

/**
    @Summary
        Set LCD module power mode for A interval.
        
    @Description
        This routine set the LCD module reference ladder A time
        power control.
        
    @Preconditions
        None.

    @Param
        Pass the power bits value.

    @Returns
        None.
      
    @Example
        <code>
        LCD_SetIntervalAPowerMode (value);
        </code>     
*/
void LCD_SetIntervalAPowerMode (unsigned int value);

/**
    @Summary
        Set LCD module power mode for B interval.
        
    @Description
        This routine set the LCD module reference ladder B time
        power control.
        
    @Preconditions
        None.

    @Param
        Pass the power bits value.

    @Returns
        None.
      
    @Example
        <code>
        LCD_SetIntervalBPowerMode (value);
        </code>     
*/
void LCD_SetIntervalBPowerMode (unsigned int value);

/**
    @Summary
        Set LCD module power distribution.
        
    @Description
        This routine set the LCD module power distribution during
        waveform intervals.
        
    @Preconditions
        None.

    @Param
        Pass the power bits value.

    @Returns
        None.
      
    @Example
        <code>
        LCD_SetPowerDistribution (value);
        </code>     
*/
void LCD_SetPowerDistribution (unsigned int value);

/**
    @Summary
        Returns true if the LCD module is active, otherwise false.
        
    @Description
        This routine is used to determine if the LCD module is active.
        
    @Preconditions
        None.

    @Param
        Node.

    @Returns
        true  - If module is active.
        false - If module is not active.
      
    @Example
        <code>
         LCD_Initialize();
         while(!LCD_IsActive()); // wait until the module is available
        </code>     
*/
bool LCD_IsActive (void);


 /**
   @Summary
     Implements ISR

   @Description
     This routine is used to implement the ISR for the interrupt-driven
     implementations.

   @Returns
     None

   @Param
     None
 */
 void LCD_ISR(void);

#endif /*_LCD_H*/

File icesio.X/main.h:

/*
 * File:   main.h
 * Author: ice
 *
 * Created on February 5, 2019, 3:06 PM
 */

#ifndef MAIN_H
#define MAIN_H

#include <stdint.h>

#define TICK_MS     100     // main loop period, ms

// Side buttons (all schematics V1/V2: MODE -> RH0/COM4, PRGM -> RH1/COM5),
// active low: a press connects the pin to GND (see buttons.c)
#define CASIO_MODE  PORTHbits.RH0
#define CASIO_PRGM  PORTHbits.RH1

// Buzzer: SIG -> RG0/SEG42 -> T1 -> L1/BUZZ (driven by PWM3 in beep.c)
#define CASIO_SIG   LATGbits.LATG0

// TODO: the pins below don't match the schematics (K2 is RG1 = UART TX2, ...) - not used yet
#define CASIO_K2    RG0
#define CASIO_K3    RG1
#define CASIO_K4    RG2
#define CASIO_K5    RG3
#define CASIO_K6    RF7
#define CASIO_K7    RF5
#define CASIO_K8    RF3
#define CASIO_K9    RF2


#endif  /* MAIN_H */

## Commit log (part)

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2019-03-12 Upload hardware
2019-05-04 shematics
2019-05-04 adding png
2019-05-04 clean
